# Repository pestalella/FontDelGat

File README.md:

# FontDelGat
La Font del Gat: a 2 channel power supply. 
Features:
  * 2 output channels, up to 30V and 3A each
  * Possibility to link the 2 channels in series or in parallel
  * User input through buttons and a rotary encoder
  * LCD display to show the voltage and current limits and the actual outputs
  * Possibility to enable or disable the outputs independently

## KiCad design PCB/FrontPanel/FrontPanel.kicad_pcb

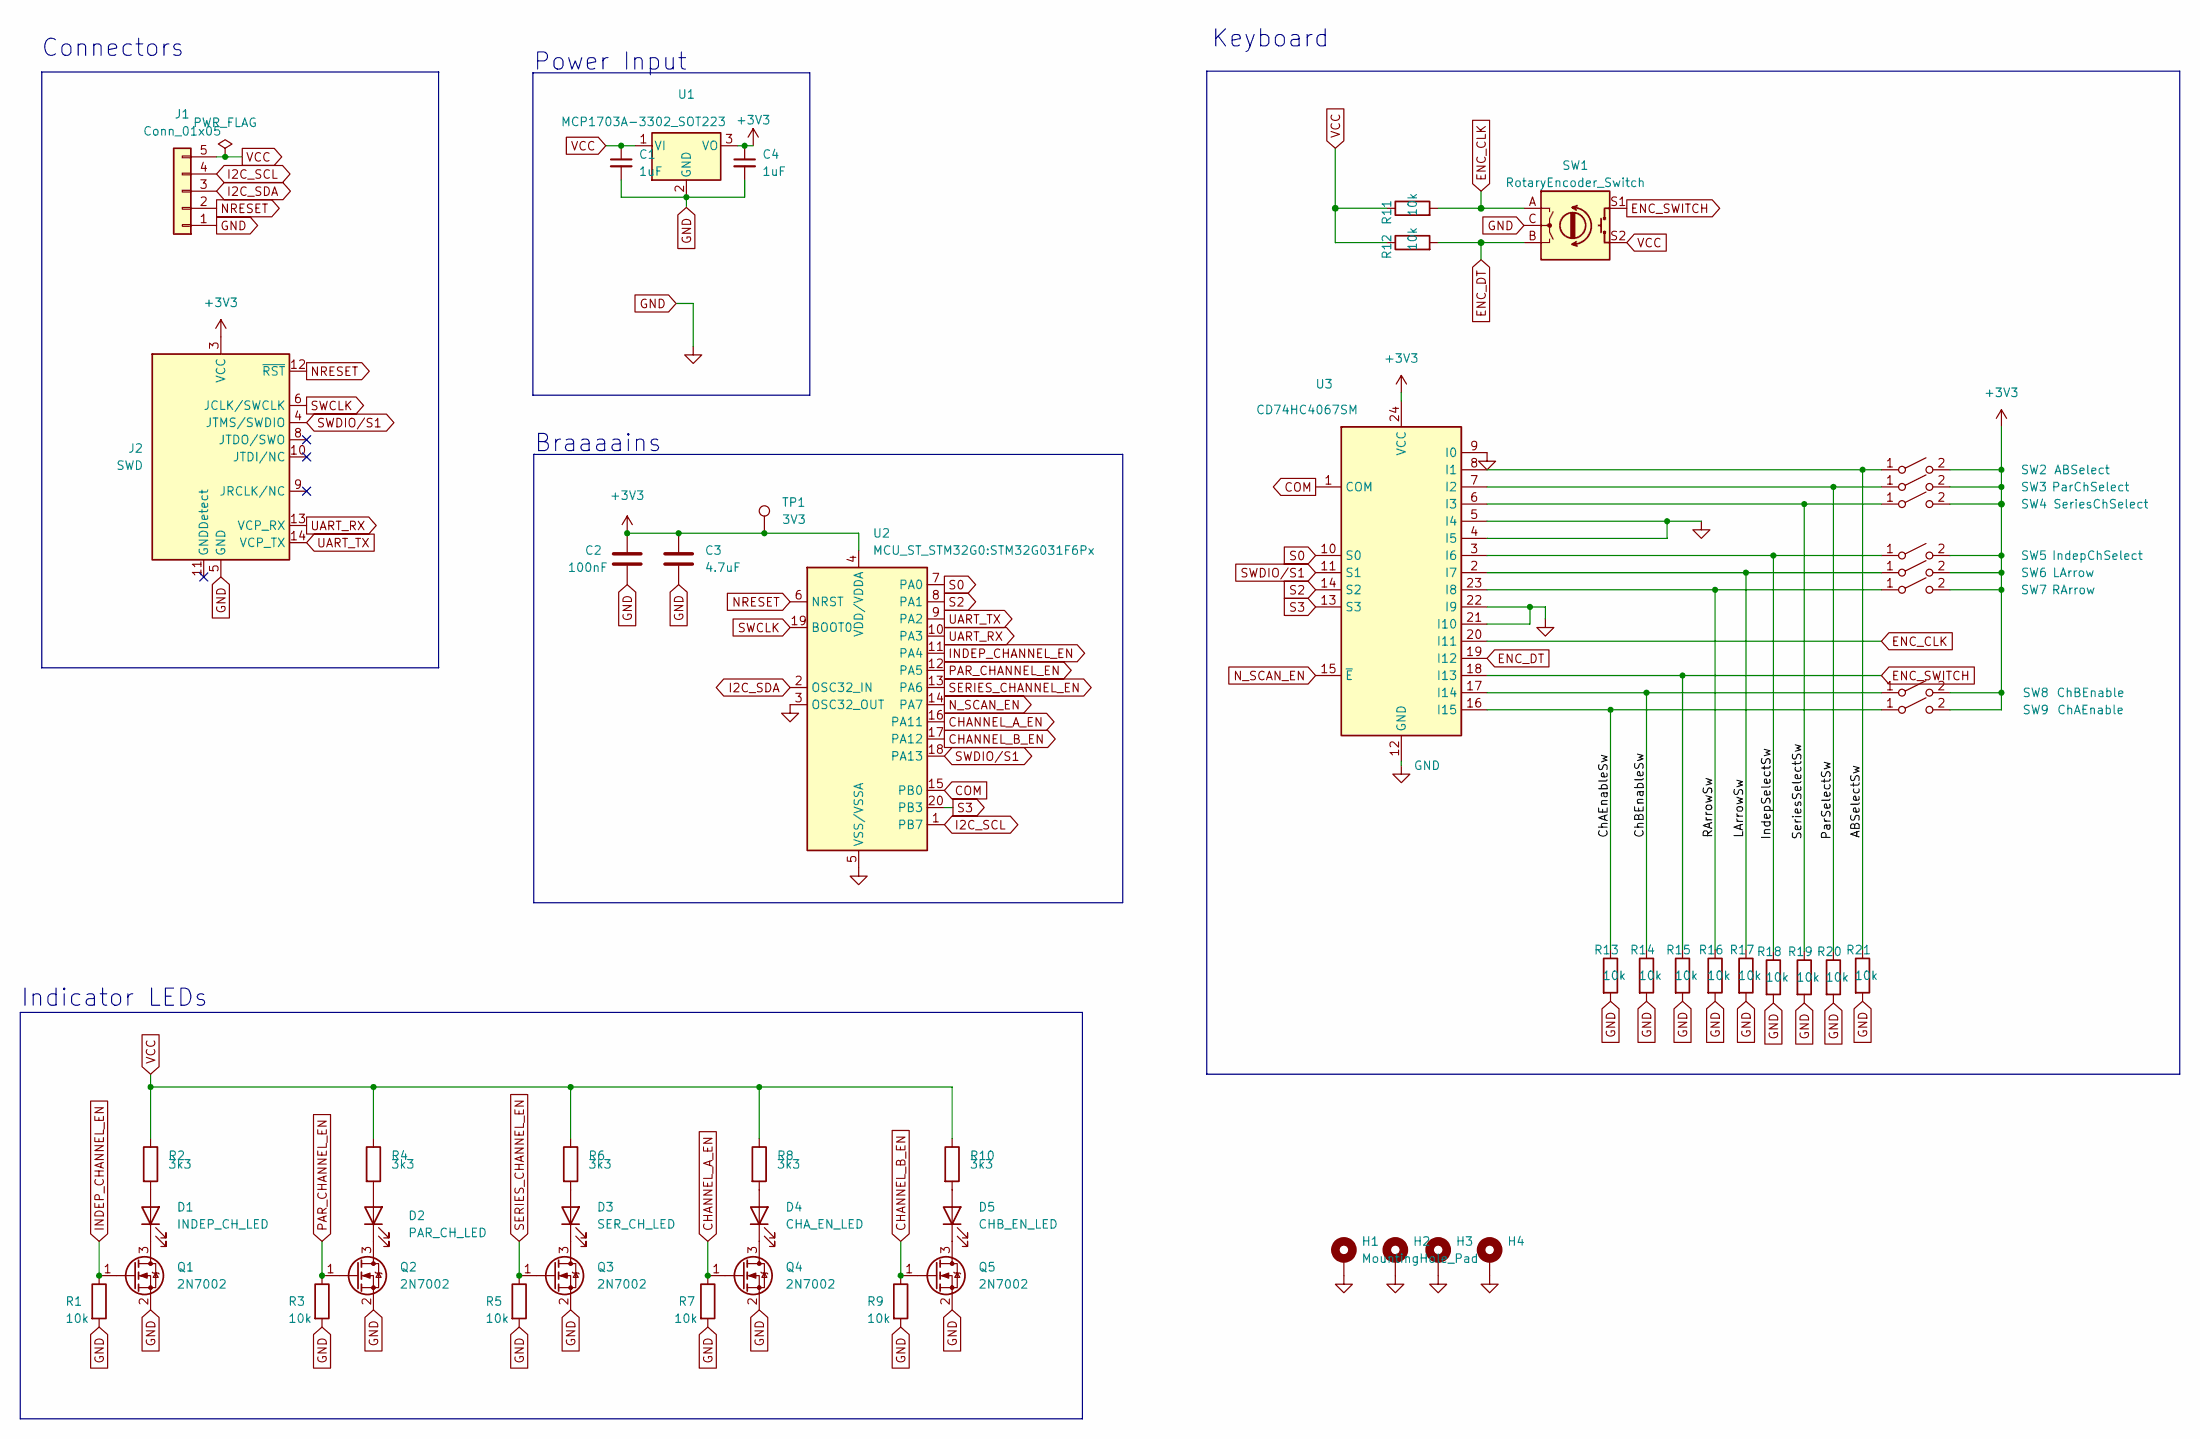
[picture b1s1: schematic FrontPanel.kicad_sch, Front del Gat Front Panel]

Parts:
C1, C4: 1uF; C_0805_2012Metric
C2: 100nF; C_0805_2012Metric_Pad1.18x1.45mm_HandSolder
C3: 4.7uF; C_0805_2012Metric_Pad1.18x1.45mm_HandSolder; JLC 0603
D1: INDEP_CH_LED; LED_0805_2012Metric_Pad1.15x1.40mm_HandSolder
D2: PAR_CH_LED; LED_0805_2012Metric_Pad1.15x1.40mm_HandSolder
D3: SER_CH_LED; LED_0805_2012Metric_Pad1.15x1.40mm_HandSolder
D4: CHA_EN_LED; LED_0805_2012Metric_Pad1.15x1.40mm_HandSolder
D5: CHB_EN_LED; LED_0805_2012Metric_Pad1.15x1.40mm_HandSolder
H1: MountingHole_Pad; MountingHole_3.2mm_M3_Pad_Via
H2, H3, H4: MountingHole_3.2mm_M3_Pad_Via
J1: Conn_01x05; Molex_KK-254_AE-6410-05A_1x05_P2.54mm_Vertical
J2: SWD; PinHeader_2x07_P1.27mm_Vertical_SMD
Q1, Q2, Q3, Q4, Q5: 2N7002; SOT-23
R1, R3, R5, R7, R9, R11, R12, R13, R14, R15, R16, R17, R18, R19, R20, R21: 10k; R_0805_2012Metric_Pad1.20x1.40mm_HandSolder
R2, R4, R6, R8, R10: 3k3; R_0805_2012Metric_Pad1.20x1.40mm_HandSolder
SW1: RotaryEncoder_Switch; RotaryEncoder_Alps_EC11E-Switch_Vertical_H20mm
SW2: ABSelect; SW_PUSH_6mm
SW3: ParChSelect; SW_PUSH_6mm
SW4: SeriesChSelect; SW_PUSH_6mm
SW5: IndepChSelect; SW_PUSH_6mm
SW6: LArrow; SW_PUSH_6mm
SW7: RArrow; SW_PUSH_6mm
SW8: ChBEnable; SW_PUSH_6mm
SW9: ChAEnable; SW_PUSH_6mm
TP1: 3V3; TestPoint_THTPad_D2.0mm_Drill1.0mm
U1: MCP1703A-3302_SOT223; SOT-223-3_TabPin2
U2: MCU_ST_STM32G0:STM32G031F6Px; TSSOP-20_4.4x6.5mm_P0.65mm
U3: CD74HC4067SM; SSOP-24_5.3x8.2mm_P0.65mm

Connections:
+3V3: C2.1, C3.1, C4.1, J2.3 (VCC), SW2.2 (B), SW3.2 (B), SW4.2 (B), SW5.2 (B), SW6.2 (B), SW7.2 (B), SW8.2 (B), SW9.2 (B), TP1.1, U1.3 (VO), U2.4 (VDD/VDDA), U3.24 (VCC)
/ABSelectSw: R21.1, SW2.1 (A), U3.8 (I1)
/ChAEnableSw: R13.1, SW9.1 (A), U3.16 (I15)
/ChBEnableSw: R14.1, SW8.1 (A), U3.17 (I14)
/IndepSelectSw: R18.1, SW5.1 (A), U3.3 (I6)
/LArrowSw: R17.1, SW6.1 (A), U3.2 (I7)
/ParSelectSw: R20.1, SW3.1 (A), U3.7 (I2)
/RArrowSw: R16.1, SW7.1 (A), U3.23 (I8)
/SeriesSelectSw: R19.1, SW4.1 (A), U3.6 (I3)
CHANNEL_A_EN: Q4.1 (G), R7.1, U2.16 (PA11)
CHANNEL_B_EN: Q5.1 (G), R9.1, U2.17 (PA12)
COM: U2.15 (PB0), U3.1 (COM)
ENC_CLK: R11.2, SW1.A, U3.20 (I11)
ENC_DT: R12.2, SW1.B, U3.19 (I12)
ENC_SWITCH: R15.1, SW1.S1, U3.18 (I13)
GND: C1.2, C2.2, C3.2, C4.2, H1.1, H2.1, H3.1, H4.1, J1.1, J2.5 (GND), J2.7 (GND), Q1.2 (S), Q2.2 (S), Q3.2 (S), Q4.2 (S), Q5.2 (S), R1.2, R3.2, R5.2, R7.2, R9.2, R13.2, R14.2, R15.2, R16.2, R17.2, R18.2, R19.2, R20.2, R21.2, SW1.C, U1.2 (GND), U2.3 (OSC32_OUT), U2.5 (VSS/VSSA), U3.4 (I5), U3.5 (I4), U3.9 (I0), U3.12 (GND), U3.21 (I10), U3.22 (I9)
I2C_SCL: J1.4, U2.1 (PB7)
I2C_SDA: J1.3, U2.2 (OSC32_IN)
INDEP_CHANNEL_EN: Q1.1 (G), R1.1, U2.11 (PA4)
NRESET: J1.2, J2.12 (~RST), U2.6 (NRST)
N_SCAN_EN: U2.14 (PA7), U3.15 (~E)
unnamed: D1.1 (K), Q1.3 (D)
unnamed: D1.2 (A), R2.2
unnamed: D2.1 (K), Q2.3 (D)
unnamed: D2.2 (A), R4.2
unnamed: D3.1 (K), Q3.3 (D)
unnamed: D3.2 (A), R6.2
unnamed: D4.1 (K), Q4.3 (D)
unnamed: D4.2 (A), R8.2
unnamed: D5.1 (K), Q5.3 (D)
unnamed: D5.2 (A), R10.2
PAR_CHANNEL_EN: Q2.1 (G), R3.1, U2.12 (PA5)
S0: U2.7 (PA0), U3.10 (S0)
S2: U2.8 (PA1), U3.14 (S2)
S3: U2.20 (PB3), U3.13 (S3)
SERIES_CHANNEL_EN: Q3.1 (G), R5.1, U2.13 (PA6)
SWCLK: J2.6 (JCLK/SWCLK), U2.19 (BOOT0)
SWDIO/S1: J2.4 (JTMS/SWDIO), U2.18 (PA13), U3.11 (S1)
UART_RX: J2.13 (VCP_RX), U2.10 (PA3)
UART_TX: J2.14 (VCP_TX), U2.9 (PA2)
VCC: C1.1, J1.5, R2.1, R4.1, R6.1, R8.1, R10.1, R11.1, R12.1, SW1.S2, U1.1 (VI)

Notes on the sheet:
Keyboard
Braaaains
Indicator LEDs
Power Input
Connectors

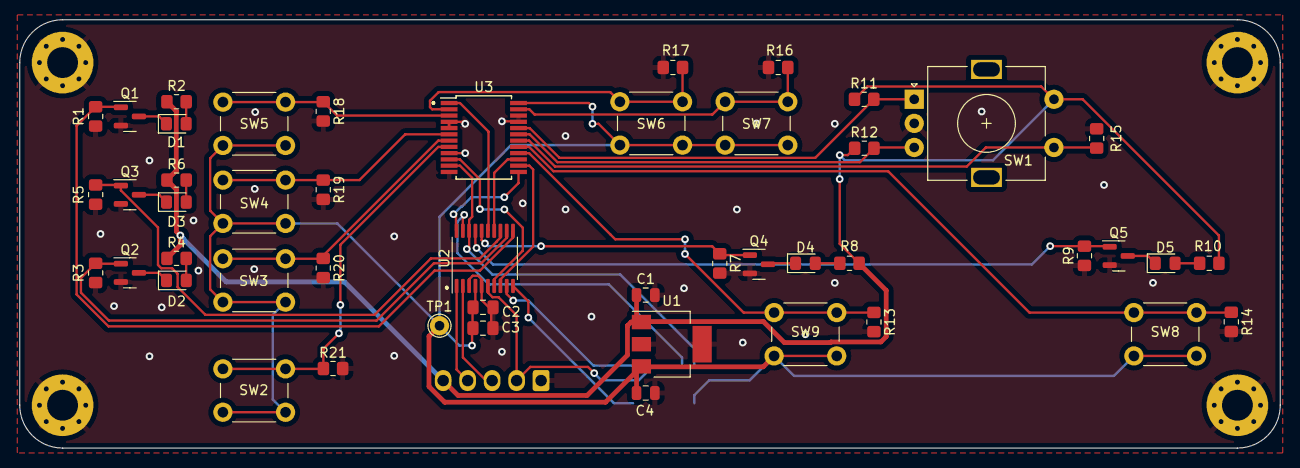
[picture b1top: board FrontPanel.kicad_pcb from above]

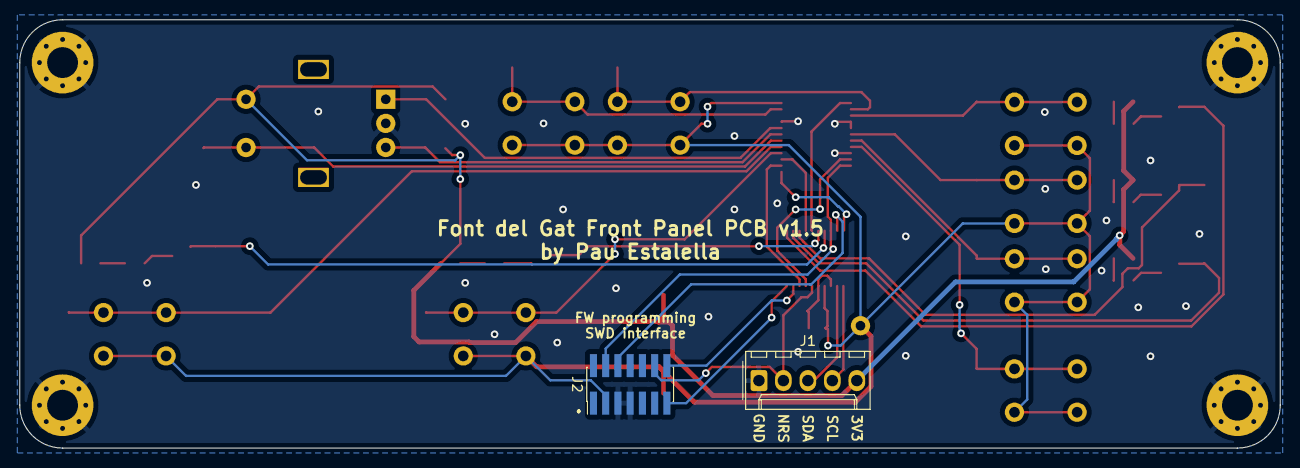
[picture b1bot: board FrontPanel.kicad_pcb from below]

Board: 2 copper layers, 130.8 x 44.5 mm, 54 parts (2 on the bottom side), 41 nets.

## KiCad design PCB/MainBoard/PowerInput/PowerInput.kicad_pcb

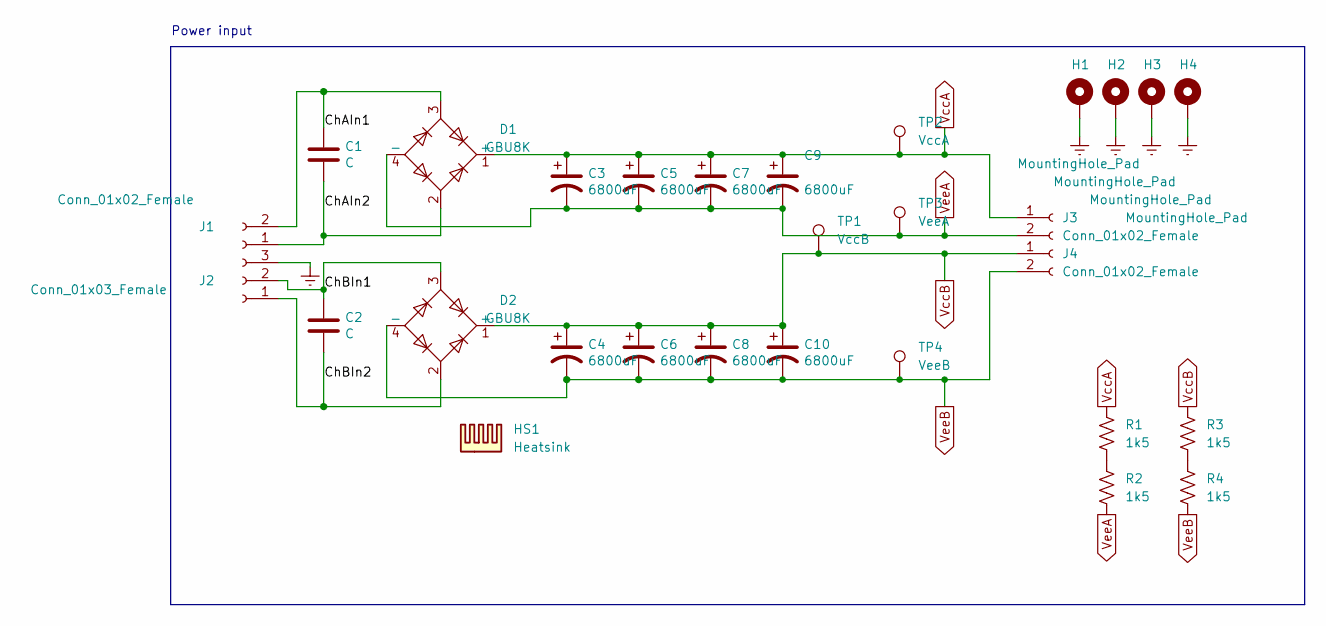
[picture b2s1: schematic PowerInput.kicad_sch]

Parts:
C1, C2: C; C_Rect_L18.0mm_W6.0mm_P15.00mm_FKS3_FKP3
C3, C4, C5, C6, C7, C8, C9, C10: 6800uF; CP_Radial_D30.0mm_P10.00mm_SnapIn
D1, D2: GBU8K; Diode_Bridge_Vishay_GBU
H1, H2, H3, H4: MountingHole_Pad; MountingHole_4.3mm_M4_Pad_Via
HS1: Heatsink; Heatsink_custom_85x4mm_3xFixationM3
J1, J3, J4: Conn_01x02_Female; PhoenixContact_MSTBVA_2,5_2-G-5,08_1x02_P5.08mm_Vertical
J2: Conn_01x03_Female; PhoenixContact_MSTBVA_2,5_3-G-5,08_1x03_P5.08mm_Vertical
R1, R2, R3, R4: 1k5; R_Axial_DIN0414_L11.9mm_D4.5mm_P20.32mm_Horizontal
TP1: VccB; TestPoint_Pad_D2.0mm
TP2: VccA; TestPoint_Pad_D2.0mm
TP3: VeeA; TestPoint_Pad_D2.0mm
TP4: VeeB; TestPoint_Pad_D2.0mm

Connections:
/ChAIn1: C1.1, D1.3, J1.2
/ChAIn2: C1.2, D1.2, J1.1
/ChBIn1: C2.1, D2.3, J2.2
/ChBIn2: C2.2, D2.2, J2.1
Earth: H1.1, H2.1, H3.1, H4.1, J2.3
unnamed: R1.2, R2.1
unnamed: R3.2, R4.1
VccA: C3.1, C5.1, C7.1, C9.1, D1.1 (+), J3.1, R1.1, TP2.1
VccB: C4.1, C6.1, C8.1, C10.1, D2.1 (+), J4.1, R3.1, TP1.1
VeeA: C3.2, C5.2, C7.2, C9.2, D1.4 (-), J3.2, R2.2, TP3.1
VeeB: C4.2, C6.2, C8.2, C10.2, D2.4 (-), J4.2, R4.2, TP4.1

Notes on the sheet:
Power input

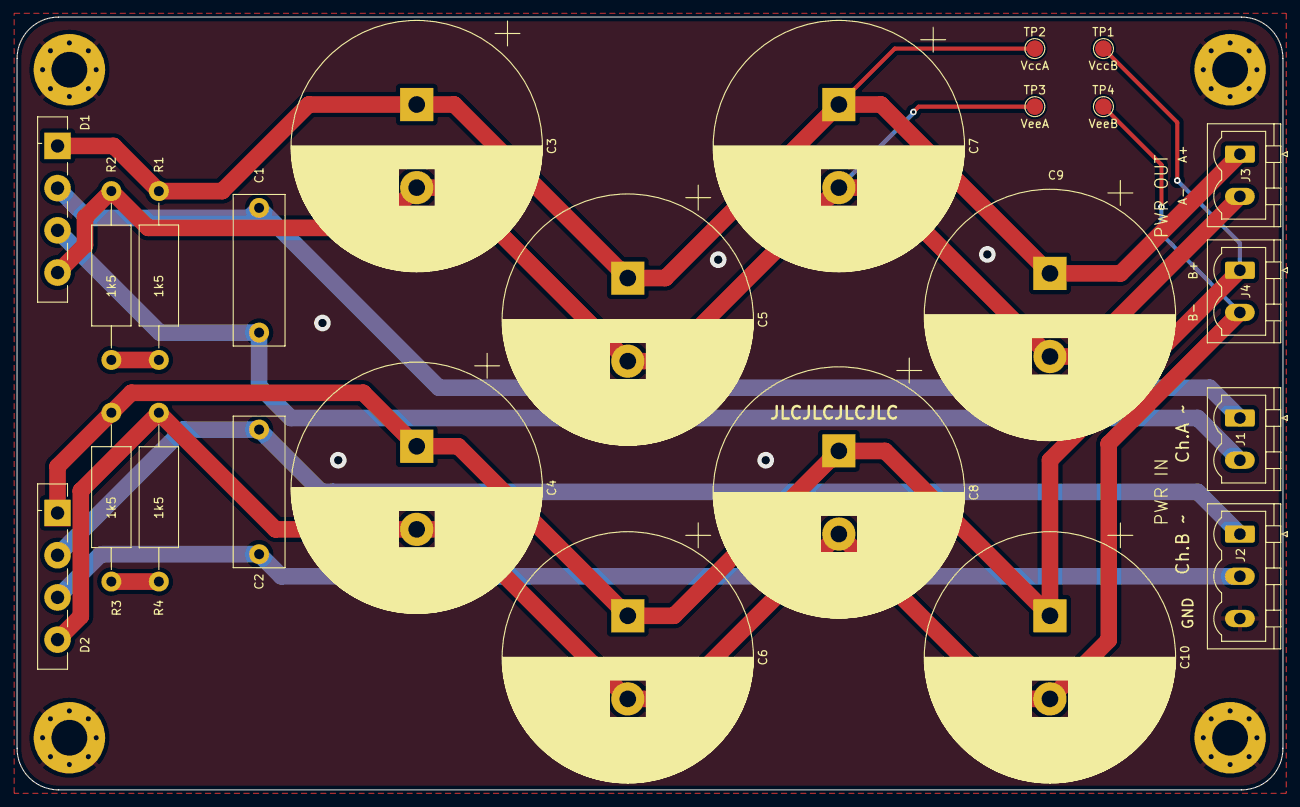
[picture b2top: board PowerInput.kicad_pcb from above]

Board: 2 copper layers, 152.3 x 93.0 mm, 29 parts (0 on the bottom side), 11 nets.

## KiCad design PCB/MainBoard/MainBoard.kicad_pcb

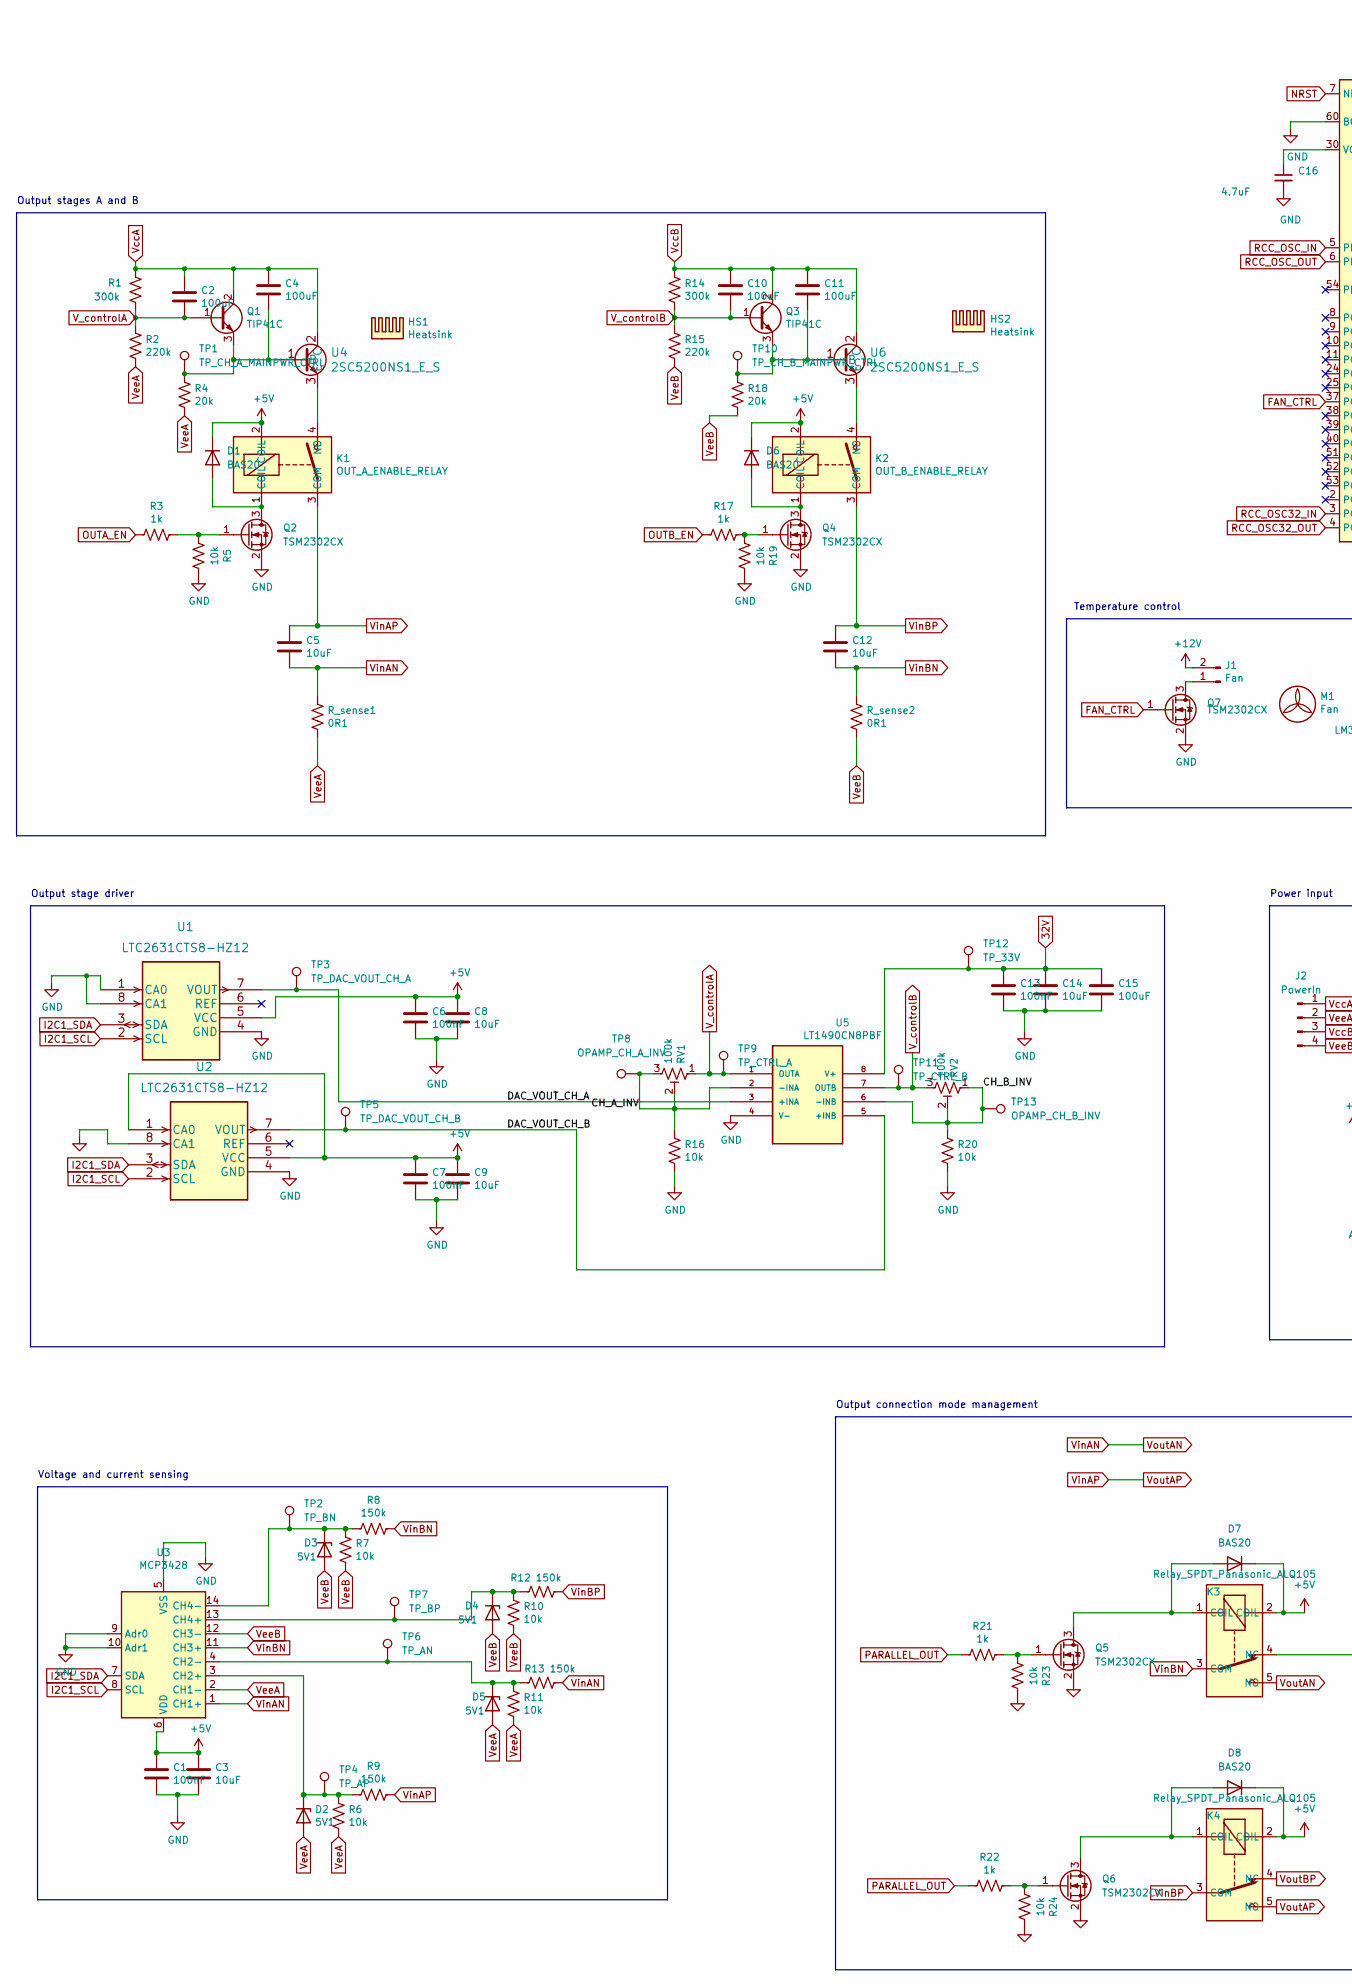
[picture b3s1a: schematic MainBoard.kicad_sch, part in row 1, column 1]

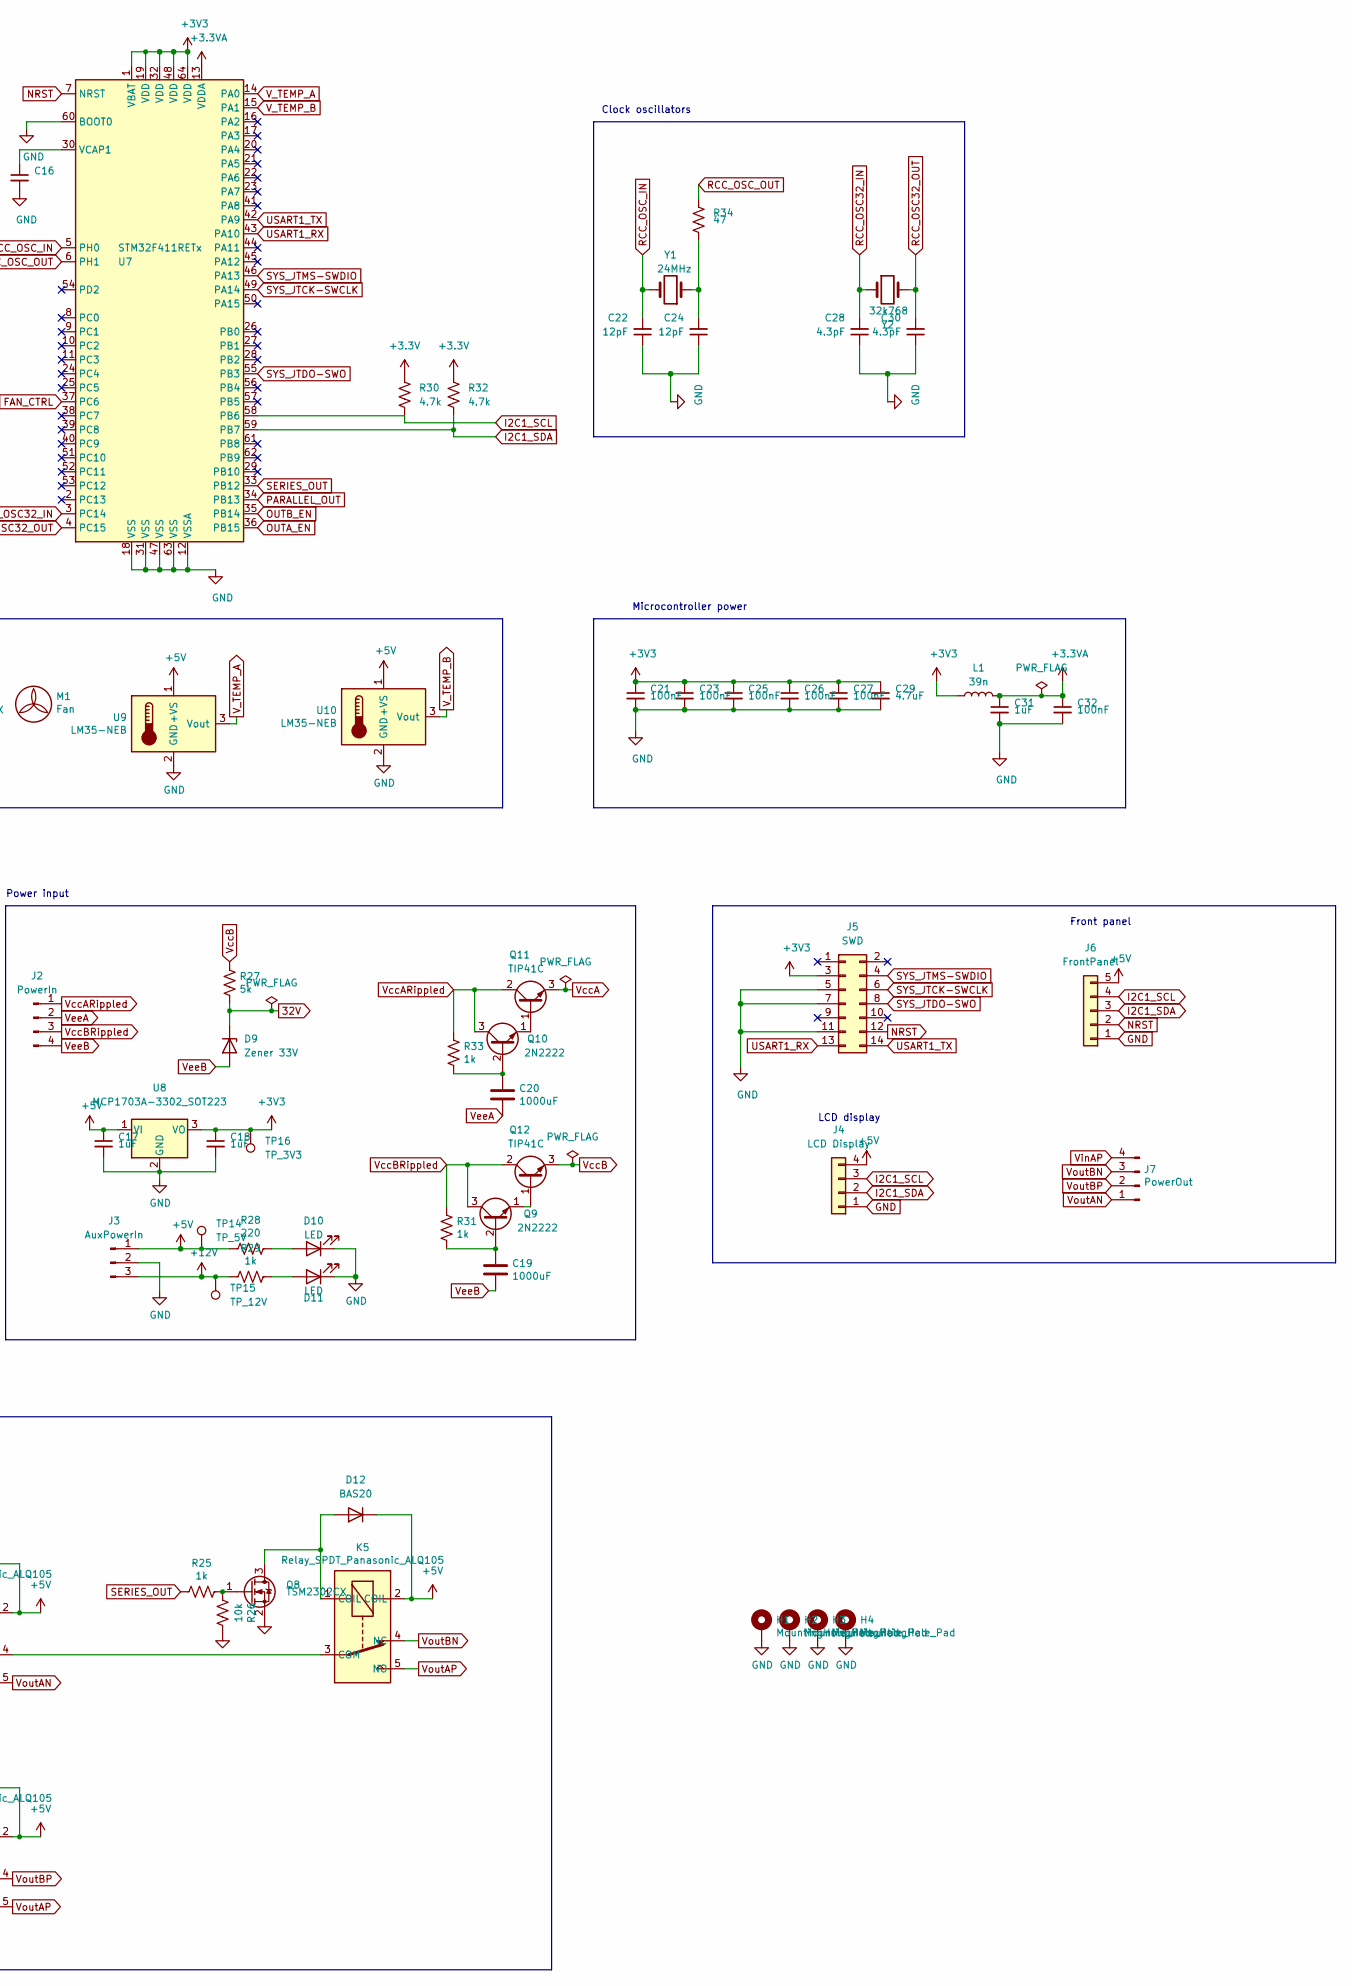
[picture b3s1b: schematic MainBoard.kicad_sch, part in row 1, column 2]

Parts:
C1, C6, C7, C13, C21, C23, C25, C26, C27, C32: 100nF; C_0603_1608Metric_Pad1.08x0.95mm_HandSolder; LCSC C14663
C2, C4, C10, C11, C15: 100uF; CP_Radial_D8.0mm_P3.80mm
C3, C8, C9: 10uF; C_1206_3216Metric_Pad1.33x1.80mm_HandSolder; LCSC C13585
C5, C12: 10uF; CP_Radial_D5.0mm_P2.00mm
C14: 10uF; C_1206_3216Metric_Pad1.42x1.75mm_HandSolder; LCSC C13585
C16, C29: 4.7uF; C_0603_1608Metric_Pad1.08x0.95mm_HandSolder; LCSC C19666
C17, C18: 1uF; C_0805_2012Metric; LCSC C28323
C19, C20: 1000uF; CP_Radial_D16.0mm_P7.50mm
C22, C24: 12pF; C_0603_1608Metric_Pad1.08x0.95mm_HandSolder
C28, C30: 4.3pF; C_0603_1608Metric_Pad1.08x0.95mm_HandSolder
C31: 1uF; C_1206_3216Metric_Pad1.33x1.80mm_HandSolder; LCSC C1848
D1, D6, D7, D8, D12: BAS20; SOT-23
D2, D3, D4, D5: 5V1; D_SOD-123
D9: Zener 33V; D_DO-35_SOD27_P10.16mm_Horizontal
D10, D11: LED; LED_0805_2012Metric_Pad1.15x1.40mm_HandSolder
H1, H2, H3, H4: MountingHole_Pad; MountingHole_4.3mm_M4_Pad_Via
HS1, HS2: Heatsink; Heatsink_100x36mm_2xfixations_HorizAirflow
J1: Fan; JST_EH_B2B-EH-A_1x02_P2.50mm_Vertical
J2: PowerIn; PhoenixContact_MSTBVA_2,5_4-G-5,08_1x04_P5.08mm_Vertical
J3: AuxPowerIn; PhoenixContact_MSTBVA_2,5_3-G-5,08_1x03_P5.08mm_Vertical
J4: LCD Display; Molex_KK-254_AE-6410-04A_1x04_P2.54mm_Vertical
J5: SWD; PinHeader_2x07_P1.27mm_Vertical_SMD
J6: FrontPanel; Molex_KK-254_AE-6410-05A_1x05_P2.54mm_Vertical
J7: PowerOut; PhoenixContact_MSTBVA_2,5_4-G-5,08_1x04_P5.08mm_Vertical
K1: OUT_A_ENABLE_RELAY; Relay_SPST_Panasonic_ALQ305
K2: OUT_B_ENABLE_RELAY; Relay_SPST_Panasonic_ALQ305
K3, K4, K5: Relay_SPDT_Panasonic_ALQ105; Relay_SPDT_Panasonic-ALQ105
L1: 39n; L_0805_2012Metric_Pad1.15x1.40mm_HandSolder
M1: Fan; Fan_Orion_OD7020_vertical
Q1, Q3, Q11, Q12: TIP41C; TO-220-3_Vertical
Q2, Q4, Q5, Q6, Q7, Q8: TSM2302CX; SOT-23
Q9, Q10: 2N2222; TO-92_HandSolder
R1, R14: 300k; R_0805_2012Metric_Pad1.20x1.40mm_HandSolder; LCSC C17616
R2, R15: 220k; R_0805_2012Metric_Pad1.20x1.40mm_HandSolder; LCSC C17556
R3, R17, R21, R22, R25, R29, R31, R33: 1k; R_0805_2012Metric_Pad1.20x1.40mm_HandSolder; LCSC C17513
R4, R18: 20k; R_0805_2012Metric_Pad1.20x1.40mm_HandSolder; LCSC C4328
R5, R6, R7, R10, R11, R16, R19, R20, R23, R24, R26: 10k; R_0805_2012Metric_Pad1.20x1.40mm_HandSolder; LCSC C17414
R8, R9, R12, R13: 150k; R_0805_2012Metric_Pad1.20x1.40mm_HandSolder; LCSC C17470
R27: 5k; R_Axial_DIN0207_L6.3mm_D2.5mm_P10.16mm_Horizontal
R28: 220; R_0805_2012Metric_Pad1.20x1.40mm_HandSolder; LCSC C17557
R30, R32: 4.7k; R_0805_2012Metric_Pad1.20x1.40mm_HandSolder; LCSC C17673
R34: 47; R_0805_2012Metric_Pad1.20x1.40mm_HandSolder; LCSC C17714
RV1, RV2: 100k; Potentiometer_Panasonic_EVM1D_Vertical
R_sense1, R_sense2: 0R1; R_Bare_Metal_Element_L21.3mm_W4.8mm_P20.30mm
TP1: TP_CH_A_MAINPWR_CTRL; TestPoint_THTPad_D2.0mm_Drill1.0mm
TP2: TP_BN; TestPoint_THTPad_D2.0mm_Drill1.0mm
TP3: TP_DAC_VOUT_CH_A; TestPoint_THTPad_D2.0mm_Drill1.0mm
TP4: TP_AP; TestPoint_THTPad_D2.0mm_Drill1.0mm
TP5: TP_DAC_VOUT_CH_B; TestPoint_THTPad_D2.0mm_Drill1.0mm
TP6: TP_AN; TestPoint_THTPad_D2.0mm_Drill1.0mm
TP7: TP_BP; TestPoint_THTPad_D2.0mm_Drill1.0mm
TP8: OPAMP_CH_A_INV; TestPoint_THTPad_D2.0mm_Drill1.0mm
TP9: TP_CTRL_A; TestPoint_THTPad_D2.0mm_Drill1.0mm
TP10: TP_CH_B_MAINPWR_CTRL; TestPoint_THTPad_D2.0mm_Drill1.0mm
TP11: TP_CTRL_B; TestPoint_THTPad_D2.0mm_Drill1.0mm
TP12: TP_33V; TestPoint_THTPad_D2.0mm_Drill1.0mm
TP13: OPAMP_CH_B_INV; TestPoint_THTPad_D2.0mm_Drill1.0mm
TP14: TP_5V; TestPoint_THTPad_D2.0mm_Drill1.0mm
TP15: TP_12V; TestPoint_THTPad_D2.0mm_Drill1.0mm
TP16: TP_3V3; TestPoint_THTPad_D2.0mm_Drill1.0mm
U1, U2: LTC2631CTS8-HZ12; ltc2631cts8-hz12-trmpbf
U3: MCP3428; SOIC-14_3.9x8.7mm_P1.27mm; LCSC C560166
U4, U6: 2SC5200NS1_E_S
U5: LT1490CN8PBF; SOIC-8_3.9x4.9mm_P1.27mm; LCSC C664001
U7: STM32F411RETx; LQFP-64_10x10mm_P0.5mm; LCSC C94355
U8: MCP1703A-3302_SOT223; SOT-223-3_TabPin2
U9, U10: LM35-NEB; TO-220-3_Vertical
Y1: 24MHz; Crystal_HC49-U_Vertical
Y2: 32k768; Crystal_C38-LF_D3.0mm_L8.0mm_Horizontal

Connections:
32V: C13.1, C14.1, C15.1, D9.1 (K), R27.2, TP12.1, U5.8 (V+)
+3.3VA: C31.1, C32.1, L1.2, U7.13 (VDDA)
+5V: C1.1, C3.1, C6.1, C7.1, C8.1, C9.1, C17.1, D1.3 (K), D6.3 (K), D7.3 (K), D8.3 (K), D12.3 (K), J3.1, J4.4, J6.5, K1.2 (COIL), K2.2 (COIL), K3.2 (COIL), K4.2 (COIL), K5.2 (COIL), R28.2, TP14.1, U1.5 (VCC), U2.1 (CA0), U2.5 (VCC), U3.6 (VDD), U8.1 (VI), U9.1 (+VS), U10.1 (+VS)
+12V: J1.2, J3.3, R29.2, TP15.1
/CH_A_INV: R16.1, RV1.2, RV1.3, TP8.1, U5.2 (-INA)
/CH_B_INV: R20.1, RV2.1, RV2.2, TP13.1, U5.6 (-INB)
/DAC_VOUT_CH_A: TP3.1, U1.7 (VOUT), U5.3 (+INA)
/DAC_VOUT_CH_B: TP5.1, U2.7 (VOUT), U5.5 (+INB)
FAN_CTRL: Q7.1 (G), U7.37 (PC6)
I2C1_SCL: J4.3, J6.4, R30.1, U1.2 (SCL), U2.2 (SCL), U3.8 (SCL), U7.58 (PB6)
I2C1_SDA: J4.2, J6.3, R32.2, U1.3 (SDA), U2.3 (SDA), U3.7 (SDA), U7.59 (PB7)
NRST: J5.12, J6.2, U7.7 (NRST)
unnamed: C4.2, Q1.3 (E), R4.1, TP1.1, U4.1 (B)
unnamed: C11.2, Q3.3 (E), R18.1, TP10.1, U6.1 (B)
unnamed: C16.1, U7.30 (VCAP1)
unnamed: C19.1, Q9.2 (B), R31.2
unnamed: C20.1, Q10.2 (B), R33.2
unnamed: C24.2, R34.2, Y1.1
unnamed: D1.1 (A), K1.1 (COIL), Q2.3 (D)
unnamed: D2.1 (K), R6.1, R9.2, TP4.1, U3.3 (CH2+)
unnamed: D3.1 (K), R7.1, R8.2, TP2.1, U3.14 (CH4-)
unnamed: D4.1 (K), R10.1, R12.2, TP7.1, U3.13 (CH4+)
unnamed: D5.1 (K), R11.1, R13.2, TP6.1, U3.4 (CH2-)
unnamed: D6.1 (A), K2.1 (COIL), Q4.3 (D)
unnamed: D7.1 (A), K3.1 (COIL), Q5.3 (D)
unnamed: D8.1 (A), K4.1 (COIL), Q6.3 (D)
unnamed: D10.2 (A), R28.1
unnamed: D11.2 (A), R29.1
unnamed: D12.1 (A), K5.1 (COIL), Q8.3 (D)
unnamed: J1.1, Q7.3 (D)
unnamed: K1.4 (NO), U4.3 (E)
unnamed: K2.4 (NO), U6.3 (E)
unnamed: K3.4 (NC), K5.3 (COM)
unnamed: Q2.1 (G), R3.1, R5.2
unnamed: Q4.1 (G), R17.1, R19.2
unnamed: Q5.1 (G), R21.1, R23.2
unnamed: Q6.1 (G), R22.1, R24.2
unnamed: Q8.1 (G), R25.1, R26.2
unnamed: Q10.1 (E), Q11.1 (B)
unnamed: Q9.1 (E), Q12.1 (B)
OUTA_EN: R3.2, U7.36 (PB15)
OUTB_EN: R17.2, U7.35 (PB14)
PARALLEL_OUT: R21.2, R22.2, U7.34 (PB13)
RCC_OSC32_IN: C28.2, U7.3 (PC14), Y2.1
RCC_OSC32_OUT: C30.2, U7.4 (PC15), Y2.2
RCC_OSC_IN: C22.2, U7.5 (PH0), Y1.2
RCC_OSC_OUT: R34.1, U7.6 (PH1)
SERIES_OUT: R25.2, U7.33 (PB12)
SYS_JTCK-SWCLK: J5.6, U7.49 (PA14)
SYS_JTDO-SWO: J5.8, U7.55 (PB3)
SYS_JTMS-SWDIO: J5.4, U7.46 (PA13)
USART1_RX: J5.13, U7.43 (PA10)
USART1_TX: J5.14, U7.42 (PA9)
V_TEMP_A: U7.14 (PA0), U9.3 (Vout)
V_TEMP_B: U7.15 (PA1), U10.3 (Vout)
V_controlA: C2.2, Q1.1 (B), R1.2, R2.1, RV1.1, TP9.1, U5.1 (OUTA)
V_controlB: C10.2, Q3.1 (B), R14.2, R15.1, RV2.3, TP11.1, U5.7 (OUTB)
VccA: C2.1, C4.1, Q1.2 (C), Q11.3 (E), R1.1, U4.2 (C)
VccARippled: J2.1, Q10.3 (C), Q11.2 (C), R33.1
VccB: C10.1, C11.1, Q3.2 (C), Q12.3 (E), R14.1, R27.1, U6.2 (C)
VccBRippled: J2.3, Q9.3 (C), Q12.2 (C), R31.1
VeeA: C20.2, D2.2 (A), D5.2 (A), J2.2, R2.2, R4.2, R6.2, R11.2, R_sense1.2, U3.2 (CH1-)
VeeB: C19.2, D3.2 (A), D4.2 (A), D9.2 (A), J2.4, R7.2, R10.2, R15.2, R18.2, R_sense2.2, U3.12 (CH3-)
VinAN: C5.2, J7.1, K3.5 (NO), R13.1, R_sense1.1, U3.1 (CH1+)
VinAP: C5.1, J7.4, K1.3 (COM), K4.5 (NO), K5.5 (NO), R9.1
VinBN: C12.2, K3.3 (COM), R8.1, R_sense2.1, U3.11 (CH3+)
VinBP: C12.1, K2.3 (COM), K4.3 (COM), R12.1
VoutBN: J7.3, K5.4 (NC)
VoutBP: J7.2, K4.4 (NC)

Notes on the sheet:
Clock oscillators
Microcontroller power
Power input
Temperature control
Front panel
Output stage driver
Output stages A and B
LCD display
Voltage and current sensing
Output connection mode management

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
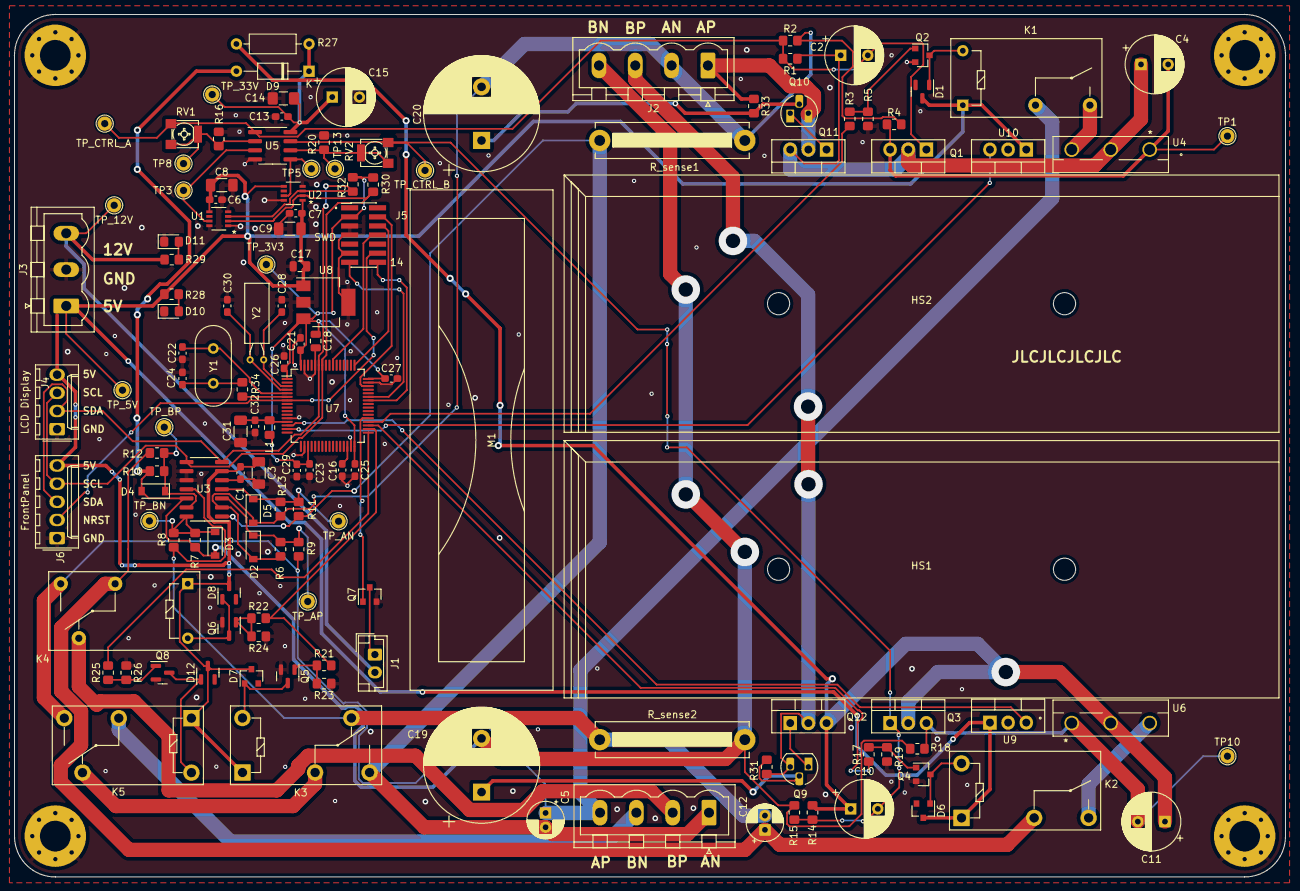
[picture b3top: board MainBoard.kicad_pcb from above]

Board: 2 copper layers, 177.8 x 120.7 mm, 142 parts (0 on the bottom side), 71 nets.

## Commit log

2022-09-11 Update README.md
    Better description in README
2022-09-11 Initial import of code
    First pieces of the main board firmware added.
2022-09-11 Improved description in README
2022-09-11 Initial import of Kicad files
    Import the main board KiCad files
2022-09-11 Import front panel design files
2022-09-11 Add MCP3428 ADC reads
    Initial code to read the output of the ADC to sample output
    voltage and current from channel A and B.
2022-09-11 Added .gitignore file
2022-09-16 Fix minor issues in PCB
    Fixed decoupling capacitors connectivbity
    Added test points to several networks
2022-09-16 Add library to drive the LTC2631 DAC
2022-09-16 Minor name change from adc to outSense
2022-09-16 Ignore more filed and directories
2022-09-16 Change 33V input resistor value
    The previous 5k1 ohm value was completely wrong.
2022-09-16 Remove cache file
2022-09-19 Add SWD connector
    USART programming is fraught with problems. It's much much
    better to use SWD through an STDC14 connector.
    Increased version number to v1.3
2022-09-19 Add cache files to .gitignore
2022-09-25 Added Front Panel FW
    Add an initial version of the front panel firmware, with very ----------
    basic functionality.
    Also a class to control the outputs of the main board.
2022-09-25 Give names to all networks a name
    Add network labels to networks that didn't yet have a name.
2022-09-25 Ignore .csv files
2022-09-26 Import power input board files
2022-09-26 Add front panel FW tester
    Read button state and change the LED state according to button presses
2022-09-26 Fixed button state updates
    Button read requests are served by interrupts, so updates to the button
    state variable need to be atomic.
2022-09-29 Fix 2N7002 footprint
    The footprint for the 2N7002 MOSFETs was taken from the one
    of a 2N7000, which has the gate and the source pins exchanged.
2022-10-23 Fixes for the front panel
    Add a 3V3 regulator to convert the 5V input.
    Fix RX/TX mix-up
    Fix footprint for one last 2N7002 mosfet
2022-11-06 Initial code for the LCD UI
    Prototype stage.
    * Read the button state and change what is displayed on the LCD.
    * Display values for the outputs (mock values)
    * Display set values for the outputs (mock values, can't set them yet)
    * Change the output mode from independent to parallel to series
2022-11-06 Refactor the Front Panel FW
    Move all the code to a separate class, leaving the .ino file mostly
    empty.
2022-11-06 Adapt BoardControl to use FrontPanel
    Instead of reading commands from the UART read the state of the
    buttons from the front panel using I2C to query the FP firmware.

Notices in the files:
parts and their libraries:
Copyright C 2016 Accelerated Designs. All rights reserved
Copyright 2016 Accelerated Designs. All rights reserved.
